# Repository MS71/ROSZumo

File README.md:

# ROSZumo
"second" Small robot based on ESP32 + ROS + ZUMO 32u4 base

Components:
* ZUMO32U4 Base (I2C Slave, Bat ADC, Motor Encoder, PWM for Lidar Stepper, l3gd20h, lsm303d, Line Sonsor, ...)
* ESP32CAM
* ESP32 WRoverwith CAM and SDCard
* driver and connector for rotating LIDAR
* 12x STM VL53L1X TOF sensor
* optional rotating Lidar with PCF8475+ULN2003 Stepper motor
* BNO055 Orientation Sensor
* STM32G081 uC
* connector for orange PI Zero H5
* connector for RPI SPI Display
* NIMH charger with front contacts
* SPI flash
* I2C level shifter
* I2C bus connector
* SPI bus connector
* low power design (shutdown and wakeup)
* optional Stereo/Quad SPI Camera

My Current Setup:
* Zumo AVR 32U4 
  * I2C slave
  * motor driver
  * bridge to all Zumo sensors (line sensor, beeper, IMU, ...)
  * battery pack 4xAA
  
* STM32G081
  * I2C slave
  * GPIO extender (e.g. for VL53L1X resets)
  * RPI LCD display driver
  * Battery changer
  * RTC
  * low power managment
  
* front VL53L1X as I2C slave

* ESP32Cam
  * I2C master
  * Camera
  * ROS2 Node
  * OTA firmware update
  
* external Linux PC or RPI3/4 as ROS2 master

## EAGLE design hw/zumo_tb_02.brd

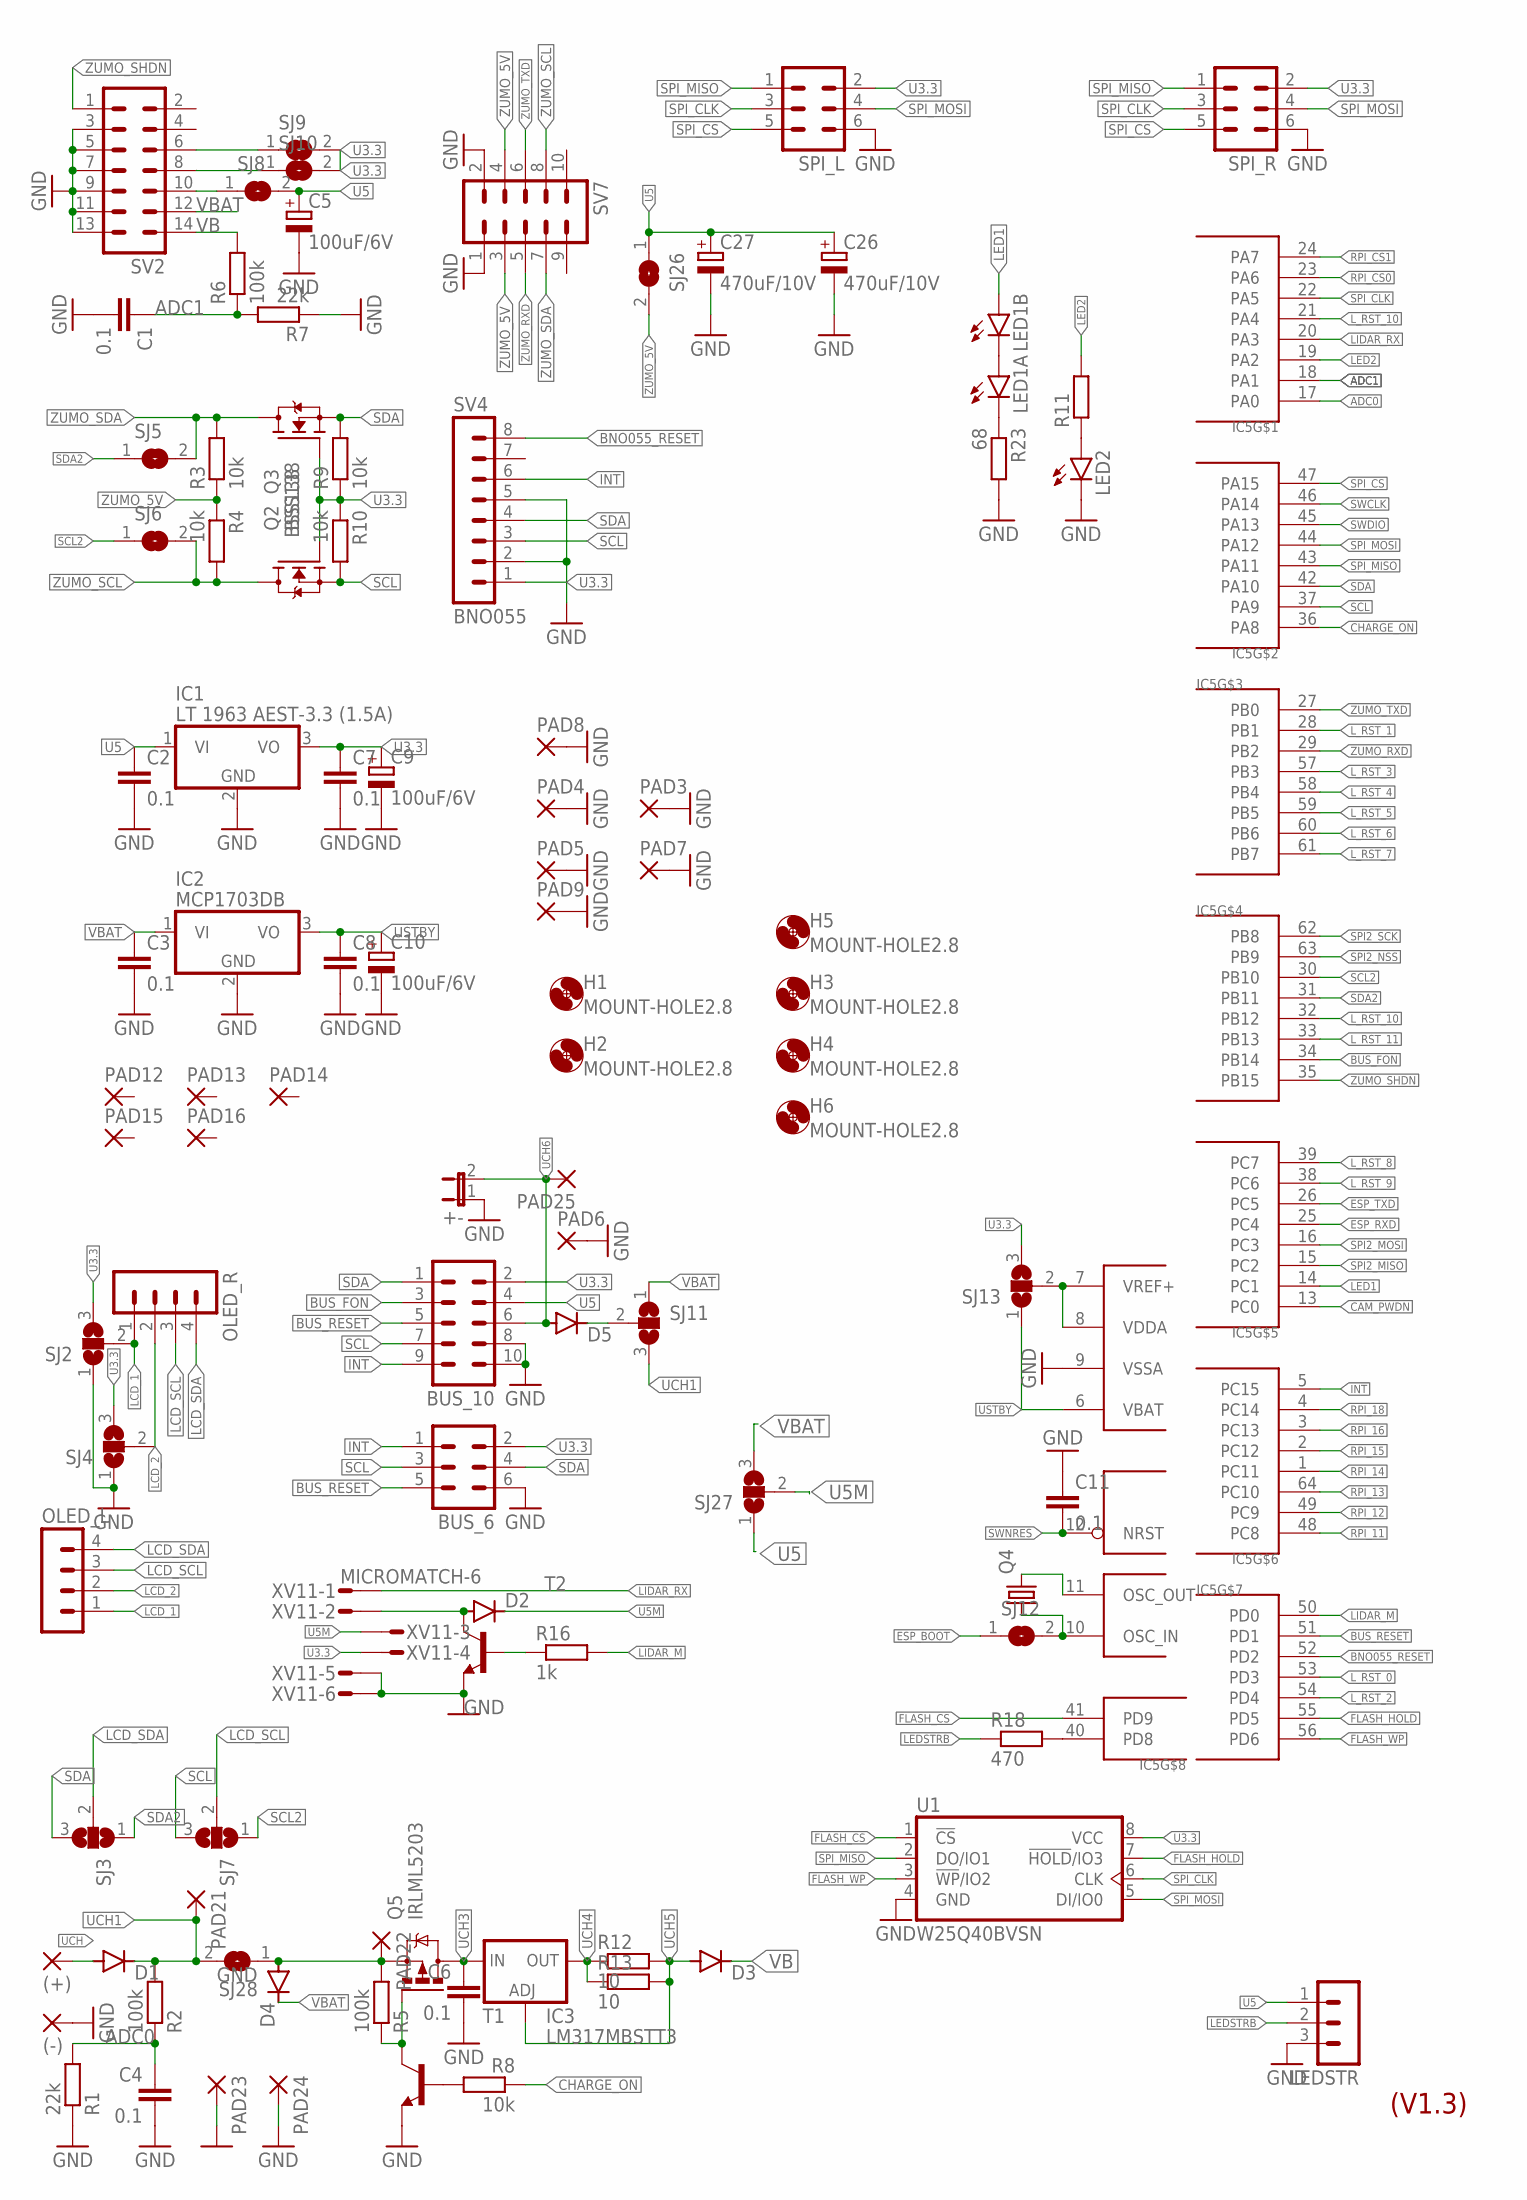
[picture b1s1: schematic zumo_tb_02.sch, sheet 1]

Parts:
(+): 3,81/1,4
(-): 3,81/1,4
+-: JP1E; JP1
BUS_6: ML6
BUS_10: ML10
C1, C2, C3, C4, C6, C7, C8, C11: 0.1; C0805
C5, C9, C10: 100uF/6V; B/3528-21R
C26, C27: 470uF/10V; SMC_D
D1, D3, D4, D5: DIODE-MELF-MLL41; MELF-MLL41
D2: DIODE-MINIMELF; MINIMELF
H1, H2, H3, H4, H5, H6: MOUNT-HOLE2.8; 2,8
IC1: LT 1963 AEST-3.3 (1.5A); SOT223
IC2: MCP1703DB; SOT223
IC3: LM317MBSTT3; SOT223
IC5: STM32G081RBT6; TQFP64
LED1A, LED1B: LED5MM
LED2: LEDCHIPLED_0805; CHIPLED_0805
LEDSTR: MA03-1
OLED_L: MA04-1
OLED_R: MA04-1
PAD3, PAD7, PAD9: 3,81/1,4
PAD4, PAD5, PAD6, PAD8: 2,15/1,0
PAD12, PAD13, PAD14, PAD15, PAD16, PAD25: 1,6/0,9
PAD21, PAD22, PAD23, PAD24: 1,6/0,8
Q2, Q3: BSS138; SOT23
Q4: CRYSTALTC26V; TC26V
Q5: IRLML5203; MICRO3
R1, R7: 22k; R0805
R2, R5, R6: 100k; R0805
R3, R4, R8, R9, R10: 10k; R0805
R11: R-EU_R0603; R0603
R12, R13: 10; R2010
R16: 1k; R0805
R18: 470; R0805
R23: 68; R0805
SJ2, SJ3, SJ4, SJ7, SJ11, SJ13, SJ27: SJ2W; SJ_2
SJ5, SJ6, SJ8, SJ9, SJ10, SJ12, SJ26, SJ28: SJ
SPI_L: ML6
SPI_R: ML6
SV2: MA07-2
SV4: BNO055; MA08-1
SV7: MA05-2
T1, T2: BC817-16-NPN-SOT23-BEC; SOT23-BEC
U1: W25Q40BVSN; SO08
XV11: MICROMATCH-6

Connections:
ADC0: C4.1, IC5.17 (PA0), R1.2, R2.1
ADC1: C1.1, IC5.18 (PA1), R6.1, R7.2
BNO055_RESET: IC5.52 (PD2), SV4.8
BUS_FON: BUS_10.3, IC5.34 (PB14)
BUS_RESET: BUS_6.5, BUS_10.5, IC5.51 (PD1)
CAM_PWDN: IC5.13 (PC0); also elsewhere on the board
CHARGE_ON: IC5.36 (PA8), R8.1
ESP_BOOT: SJ12.1; also elsewhere on the board
ESP_RXD: IC5.25 (PC4); also elsewhere on the board
ESP_TXD: IC5.26 (PC5); also elsewhere on the board
FLASH_CS: IC5.41 (PD9), U1.1 (!CS!)
FLASH_HOLD: IC5.55 (PD5), U1.7 (!HOLD!/IO3)
FLASH_WP: IC5.56 (PD6), U1.3 (!WP!/IO2)
GND: (-).1, +-.1, BUS_6.6, BUS_10.8, BUS_10.10, C1.2, C2.2, C3.2, C4.2, C5.-, C6.2, C7.2, C8.2, C9.-, C10.-, C11.1, C26.-, C27.-, IC1.2 (GND), IC2.2 (GND), IC5.9 (VSSA), LED2.C, LEDSTR.3, PAD3.1, PAD4.1, PAD5.1, PAD6.1, PAD7.1, PAD8.1, PAD9.1, PAD23.1, PAD24.1, R1.1, R7.1, R23.2, SJ2.1, SJ4.1, SPI_L.6, SPI_R.6, SV2.3, SV2.5, SV2.7, SV2.9, SV2.11, SV2.13, SV4.2, SV4.5, SV7.1, SV7.2, T1.E, T2.E, U1.4 (GND), XV11.5, XV11.6; also elsewhere on the board
INT: BUS_6.1, BUS_10.9, IC5.5 (PC15), SV4.6; also elsewhere on the board
LCD_1: OLED_L.1, OLED_R.1, SJ2.2
LCD_2: OLED_L.2, OLED_R.2, SJ4.2
LCD_SCL: OLED_L.3, OLED_R.3, SJ7.2
LCD_SDA: OLED_L.4, OLED_R.4, SJ3.2
LED1: IC5.14 (PC1), LED1B.A
LED2: IC5.19 (PA2), R11.2
LEDSTRB: LEDSTR.2, R18.1
LIDAR_M: IC5.50 (PD0), R16.2
LIDAR_RX: IC5.20 (PA3), XV11.1
L_RST_0: IC5.53 (PD3); also elsewhere on the board
L_RST_1: IC5.28 (PB1); also elsewhere on the board
L_RST_2: IC5.54 (PD4); also elsewhere on the board
L_RST_3: IC5.57 (PB3); also elsewhere on the board
L_RST_4: IC5.58 (PB4); also elsewhere on the board
L_RST_5: IC5.59 (PB5); also elsewhere on the board
L_RST_6: IC5.60 (PB6); also elsewhere on the board
L_RST_7: IC5.61 (PB7); also elsewhere on the board
L_RST_8: IC5.39 (PC7); also elsewhere on the board
L_RST_9: IC5.38 (PC6); also elsewhere on the board
L_RST_10: IC5.21 (PA4), IC5.32 (PB12); also elsewhere on the board
L_RST_11: IC5.33 (PB13); also elsewhere on the board
unnamed: IC5.11 (OSC_OUT), Q4.2
unnamed: IC5.10 (OSC_IN), Q4.1, SJ12.2
unnamed: IC5.40 (PD8), R18.2
unnamed: IC5.7 (VREF+), IC5.8 (VDDA), SJ13.2
unnamed: LED2.A, R11.1
unnamed: SJ10.1, SV2.8
unnamed: SJ9.1, SV2.6
unnamed: Q5.1 (G), R5.1, T1.C
unnamed: R8.2, T1.B
unnamed: R16.1, T2.B
unnamed: D5.C, SJ11.2
unnamed: LED1A.A, LED1B.K (C)
unnamed: LED1A.K (C), R23.1
unnamed: D2.A, T2.C, XV11.2
RPI_11: IC5.48 (PC8); also elsewhere on the board
RPI_12: IC5.49 (PC9); also elsewhere on the board
RPI_13: IC5.64 (PC10); also elsewhere on the board
RPI_14: IC5.1 (PC11); also elsewhere on the board
RPI_15: IC5.2 (PC12); also elsewhere on the board
RPI_16: IC5.3 (PC13); also elsewhere on the board
RPI_18: IC5.4 (PC14); also elsewhere on the board
RPI_CS0: IC5.23 (PA6); also elsewhere on the board
RPI_CS1: IC5.24 (PA7); also elsewhere on the board
SCL: BUS_6.3, BUS_10.7, IC5.37 (PA9), Q3.2 (S), R10.2, SJ7.3, SV4.3; also elsewhere on the board
SCL2: IC5.30 (PB10), SJ6.1, SJ7.1
SDA: BUS_6.4, BUS_10.1, IC5.42 (PA10), Q2.2 (S), R9.2, SJ3.3, SV4.4; also elsewhere on the board
SDA2: IC5.31 (PB11), SJ3.1, SJ5.1
SPI2_MISO: IC5.15 (PC2); also elsewhere on the board
SPI2_MOSI: IC5.16 (PC3); also elsewhere on the board
SPI2_NSS: IC5.63 (PB9); also elsewhere on the board
SPI2_SCK: IC5.62 (PB8); also elsewhere on the board
SPI_CLK: IC5.22 (PA5), SPI_L.3, SPI_R.3, U1.6 (CLK); also elsewhere on the board
SPI_CS: IC5.47 (PA15), SPI_L.5, SPI_R.5; also elsewhere on the board
SPI_MISO: IC5.43 (PA11), SPI_L.1, SPI_R.1, U1.2 (DO/IO1); also elsewhere on the board
SPI_MOSI: IC5.44 (PA12), SPI_L.4, SPI_R.4, U1.5 (DI/IO0); also elsewhere on the board
SWCLK: IC5.46 (PA14); also elsewhere on the board
SWDIO: IC5.45 (PA13); also elsewhere on the board
SWNRES: C11.2, IC5.12 (NRST); also elsewhere on the board
U3.3: BUS_6.2, BUS_10.2, C7.1, C9.+, IC1.3 (VO), Q2.1 (G), Q3.1 (G), R9.1, R10.1, SJ2.3, SJ4.3, SJ9.2, SJ10.2, SJ13.3, SPI_L.2, SPI_R.2, SV4.1, U1.8 (VCC), XV11.4; also elsewhere on the board
U5: BUS_10.4, C2.1, C5.+, C26.+, C27.+, IC1.1 (VI), LEDSTR.1, SJ8.2, SJ26.1, SJ27.1; also elsewhere on the board
U5M: D2.C, SJ27.2, XV11.3
UCH: (+).1, D1.A
UCH1: D1.C, PAD21.1, R2.2, SJ11.3, SJ28.2
UCH2: D4.A, PAD22.1, Q5.2 (S), R5.2, SJ28.1
UCH3: C6.1, IC3.3 (IN), Q5.3 (D)
UCH4: IC3.4 (OUT), R12.1, R13.1
UCH5: D3.A, IC3.1 (ADJ), R12.2, R13.2
UCH6: +-.2, BUS_10.6, D5.A, PAD25.1
USTBY: C8.1, C10.+, IC2.3 (VO), IC5.6 (VBAT), SJ13.1; also elsewhere on the board
VB: D3.C, R6.2, SV2.14
VBAT: C3.1, D4.C, IC2.1 (VI), SJ11.1, SJ27.3, SV2.12
VREG: SJ8.1, SV2.10
ZUMO_5V: R3.1, R4.1, SJ26.2, SV7.3, SV7.4
ZUMO_RXD: IC5.29 (PB2), SV7.5
ZUMO_SCL: Q3.3 (D), R4.2, SJ6.2, SV7.8
ZUMO_SDA: Q2.3 (D), R3.2, SJ5.2, SV7.7
ZUMO_SHDN: IC5.35 (PB15), SV2.1; also elsewhere on the board
ZUMO_TXD: IC5.27 (PB0), SV7.6

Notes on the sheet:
(V1.3)

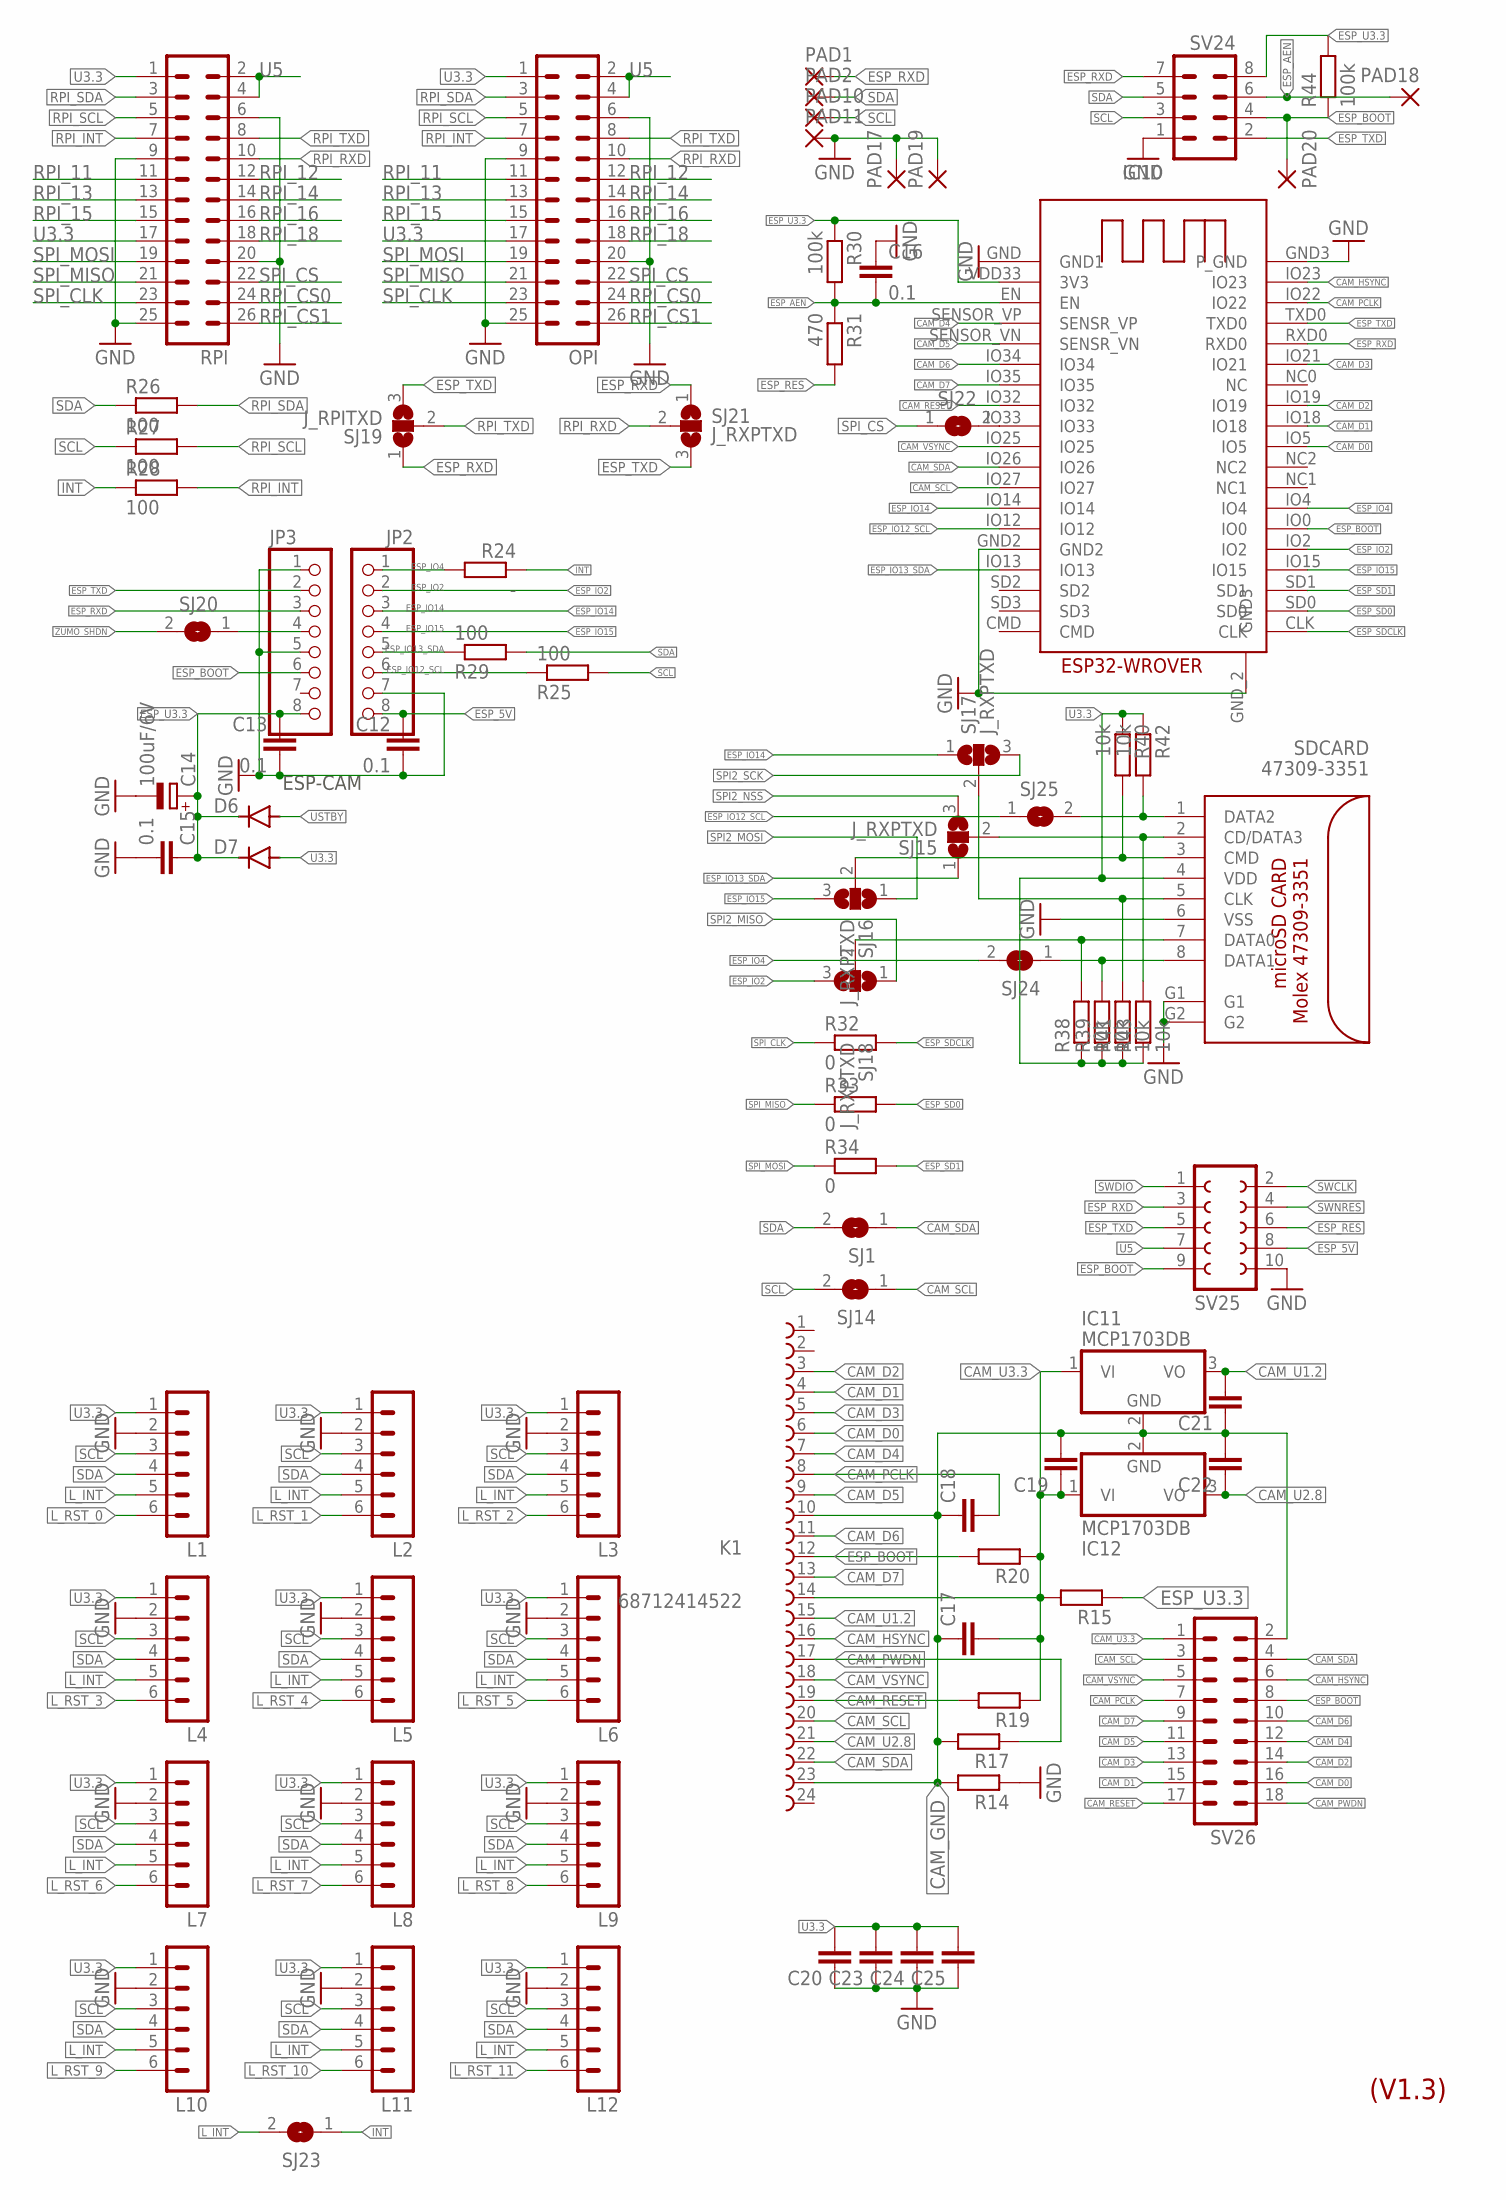
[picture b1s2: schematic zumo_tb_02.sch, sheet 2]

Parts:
C12, C13, C15, C16: 0.1; C0805
C14: 100uF/6V; B/3528-21R
C17, C18, C19, C20, C21, C22, C23, C24, C25: C-EUC0603; C0603
D6, D7: DIODE-MICROMELF-W; MICROMELF-W
IC10: ESP32-WROVER
IC11, IC12: MCP1703DB; SOT223
JP2, JP3: PINHD-1X8_2.54-SMD; 1X08SMD
K1: 68712414522
L1, L2, L3, L4, L5, L6, L7, L8, L9, L10, L11, L12: MA06-1
OPI: MA13-2
PAD1, PAD2, PAD10, PAD11, PAD17, PAD18, PAD19, PAD20: 1,6/0,9
R14, R15, R17, R19, R20: R-EU_R0603; R0603
R24: -; R0805
R25, R26, R27, R28, R29: 100; R0805
R30, R44: 100k; R0805
R31: 470; R0805
R32, R33, R34: 0; R0805
R38, R39, R40, R41, R42, R43: 10k; R0805
RPI: MA13-2
SDCARD: 47309-3351
SJ1, SJ14, SJ20, SJ22, SJ23, SJ24, SJ25: SJ
SJ15, SJ16, SJ17, SJ18, SJ21: J_RXPTXD; SJ_2
SJ19: J_RPITXD; SJ_2
SV24: MA04-2
SV25: FE05-2
SV26: MA09-2

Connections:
CAM_D0: IC10.IO5, K1.6, SV26.16
CAM_D1: IC10.IO18, K1.4, SV26.15
CAM_D2: IC10.IO19, K1.3, SV26.14
CAM_D3: IC10.IO21, K1.5, SV26.13
CAM_D4: IC10.SENSOR_VP (SENSR_VP), K1.7, SV26.12
CAM_D5: IC10.SENSOR_VN (SENSR_VN), K1.9, SV26.11
CAM_D6: IC10.IO34, K1.11, SV26.10
CAM_D7: IC10.IO35, K1.13, SV26.9
CAM_GND: C17.1, C18.1, C19.2, C21.1, C22.2, IC11.2 (GND), IC12.2 (GND), K1.10, K1.23, R14.2, R17.2, SV26.2
CAM_HSYNC: IC10.IO23, K1.16, SV26.6
CAM_PCLK: C18.2, IC10.IO22, K1.8, SV26.7
CAM_PWDN: K1.17, R17.1, SV26.18; also elsewhere on the board
CAM_RESET: IC10.IO32, K1.19, R19.2, SV26.17
CAM_SCL: IC10.IO27, K1.20, SJ14.1, SV26.3
CAM_SDA: IC10.IO26, K1.22, SJ1.1, SV26.4
CAM_U1.2: C21.2, IC11.3 (VO), K1.15
CAM_U2.8: C22.1, IC12.3 (VO), K1.21
CAM_U3.3: C17.2, C19.1, IC11.1 (VI), IC12.1 (VI), K1.14, R15.2, R19.1, R20.1, SV26.1
CAM_VSYNC: IC10.IO25, K1.18, SV26.5
ESPCAM_13: JP3.4, SJ20.1
ESP_5V: C12.1, JP2.8, SV25.8
ESP_AEN: C16.2, IC10.EN, PAD18.1, R30.2, R31.1, SV24.6
ESP_BOOT: IC10.IO0, JP3.6, K1.12, PAD20.1, R20.2, R44.1, SV24.4, SV25.9, SV26.8; also elsewhere on the board
ESP_IO2: IC10.IO2, JP2.2, SJ18.3
ESP_IO4: IC10.IO4, JP2.1, R24.2, SJ24.2
ESP_IO12_SCL: IC10.IO12, JP2.6, R25.1, SJ25.1
ESP_IO13_SDA: IC10.IO13, JP2.5, R29.1, SJ15.1
ESP_IO14: IC10.IO14, JP2.3, SJ17.1
ESP_IO15: IC10.IO15, JP2.4, SJ16.3
ESP_RES: R31.2, SV25.6
ESP_RXD: IC10.RXD0, JP3.3, PAD1.1, SJ19.1, SJ21.1, SV24.7, SV25.3; also elsewhere on the board
ESP_SD0: IC10.SD0, R33.2
ESP_SD1: IC10.SD1, R34.2
ESP_SDCLK: IC10.CLK, R32.2
ESP_TXD: IC10.TXD0, JP3.2, SJ19.3, SJ21.3, SV24.2, SV25.5; also elsewhere on the board
ESP_U3.3: C13.1, C14.+, C15.1, D6.C, D7.C, IC10.VDD33 (3V3), JP3.8, R15.1, R30.1, R44.2, SV24.8
GND: C12.2, C13.2, C14.-, C15.2, C16.1, C20.1, C23.1, C24.1, C25.1, IC10.GND (GND1), IC10.GND2, IC10.GND3 (P_GND), IC10.GND_2 (GND3), JP2.7, JP3.1, JP3.5, L1.2, L2.2, L3.2, L4.2, L5.2, L6.2, L7.2, L8.2, L9.2, L10.2, L11.2, L12.2, OPI.6, OPI.9, OPI.20, OPI.25, PAD11.1, PAD17.1, PAD19.1, R14.1, RPI.6, RPI.9, RPI.20, RPI.25, SDCARD.6 (VSS), SDCARD.G1, SDCARD.G2, SV24.1, SV25.10; also elsewhere on the board
INT: R24.1, R28.1, SJ23.1; also elsewhere on the board
L_INT: L1.5, L2.5, L3.5, L4.5, L5.5, L6.5, L7.5, L8.5, L9.5, L10.5, L11.5, L12.5, SJ23.2
L_RST_0: L1.6; also elsewhere on the board
L_RST_1: L2.6; also elsewhere on the board
L_RST_2: L3.6; also elsewhere on the board
L_RST_3: L4.6; also elsewhere on the board
L_RST_4: L5.6; also elsewhere on the board
L_RST_5: L6.6; also elsewhere on the board
L_RST_6: L7.6; also elsewhere on the board
L_RST_7: L8.6; also elsewhere on the board
L_RST_8: L9.6; also elsewhere on the board
L_RST_9: L10.6; also elsewhere on the board
L_RST_10: L11.6; also elsewhere on the board
L_RST_11: L12.6; also elsewhere on the board
unnamed: IC10.IO33, SJ22.2
RPI_11: OPI.11, RPI.11; also elsewhere on the board
RPI_12: OPI.12, RPI.12; also elsewhere on the board
RPI_13: OPI.13, RPI.13; also elsewhere on the board
RPI_14: OPI.14, RPI.14; also elsewhere on the board
RPI_15: OPI.15, RPI.15; also elsewhere on the board
RPI_16: OPI.16, RPI.16; also elsewhere on the board
RPI_18: OPI.18, RPI.18; also elsewhere on the board
RPI_CS0: OPI.24, RPI.24; also elsewhere on the board
RPI_CS1: OPI.26, RPI.26; also elsewhere on the board
RPI_INT: OPI.7, R28.2, RPI.7
RPI_RXD: OPI.10, RPI.10, SJ21.2
RPI_SCL: OPI.5, R27.2, RPI.5
RPI_SDA: OPI.3, R26.2, RPI.3
RPI_TXD: OPI.8, RPI.8, SJ19.2
SCL: L1.3, L2.3, L3.3, L4.3, L5.3, L6.3, L7.3, L8.3, L9.3, L10.3, L11.3, L12.3, PAD10.1, R25.2, R27.1, SJ14.2, SV24.3; also elsewhere on the board
SDA: L1.4, L2.4, L3.4, L4.4, L5.4, L6.4, L7.4, L8.4, L9.4, L10.4, L11.4, L12.4, PAD2.1, R26.1, R29.2, SJ1.2, SV24.5; also elsewhere on the board
SD_CLK: R41.2, SDCARD.5 (CLK), SJ17.2
SD_CMD: R40.2, SDCARD.3 (CMD), SJ16.2
SD_DAT0: R38.2, SDCARD.7 (DATA0), SJ18.2
SD_DAT1: R39.2, SDCARD.8 (DATA1), SJ24.1
SD_DAT2: R42.2, SDCARD.1 (DATA2), SJ25.2
SD_DAT3: R43.2, SDCARD.2 (CD/DATA3), SJ15.2
SPI2_MISO: SJ18.1; also elsewhere on the board
SPI2_MOSI: SJ16.1; also elsewhere on the board
SPI2_NSS: SJ15.3; also elsewhere on the board
SPI2_SCK: SJ17.3; also elsewhere on the board
SPI_CLK: OPI.23, R32.1, RPI.23; also elsewhere on the board
SPI_CS: OPI.22, RPI.22, SJ22.1; also elsewhere on the board
SPI_MISO: OPI.21, R33.1, RPI.21; also elsewhere on the board
SPI_MOSI: OPI.19, R34.1, RPI.19; also elsewhere on the board
SWCLK: SV25.2; also elsewhere on the board
SWDIO: SV25.1; also elsewhere on the board
SWNRES: SV25.4; also elsewhere on the board
U3.3: C20.2, C23.2, C24.2, C25.2, D7.A, L1.1, L2.1, L3.1, L4.1, L5.1, L6.1, L7.1, L8.1, L9.1, L10.1, L11.1, L12.1, OPI.1, OPI.17, R38.1, R39.1, R40.1, R41.1, R42.1, R43.1, RPI.1, RPI.17, SDCARD.4 (VDD); also elsewhere on the board
U5: OPI.2, OPI.4, RPI.2, RPI.4, SV25.7; also elsewhere on the board
USTBY: D6.A; also elsewhere on the board
ZUMO_SHDN: SJ20.2; also elsewhere on the board

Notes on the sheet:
ESP-CAM
(V1.3)

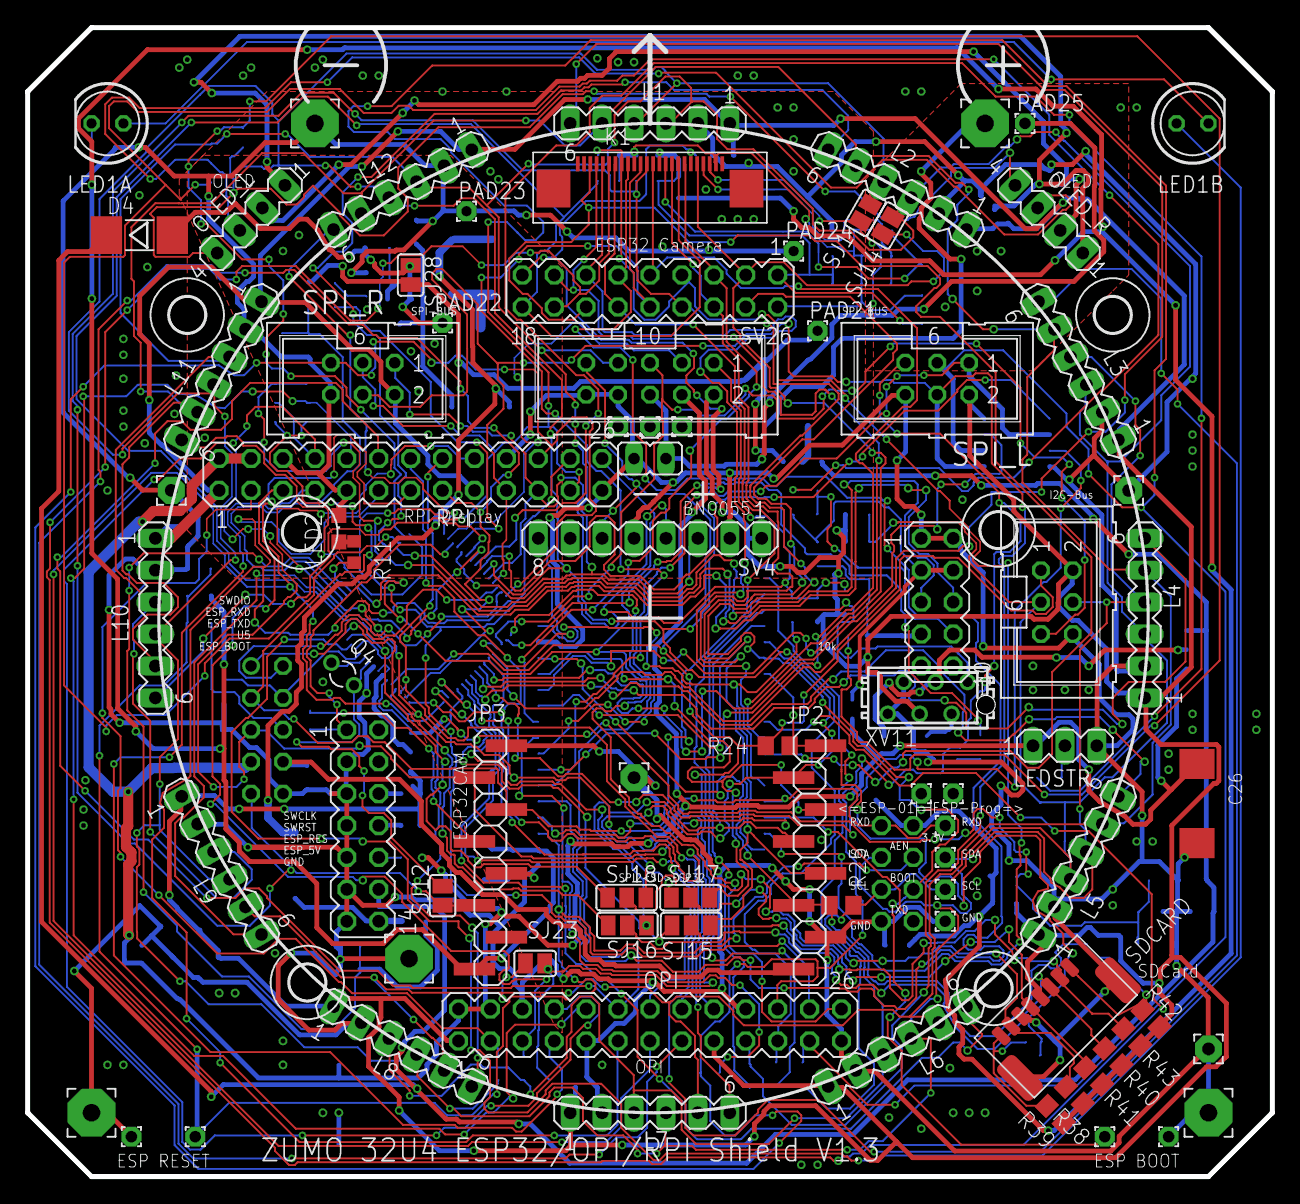
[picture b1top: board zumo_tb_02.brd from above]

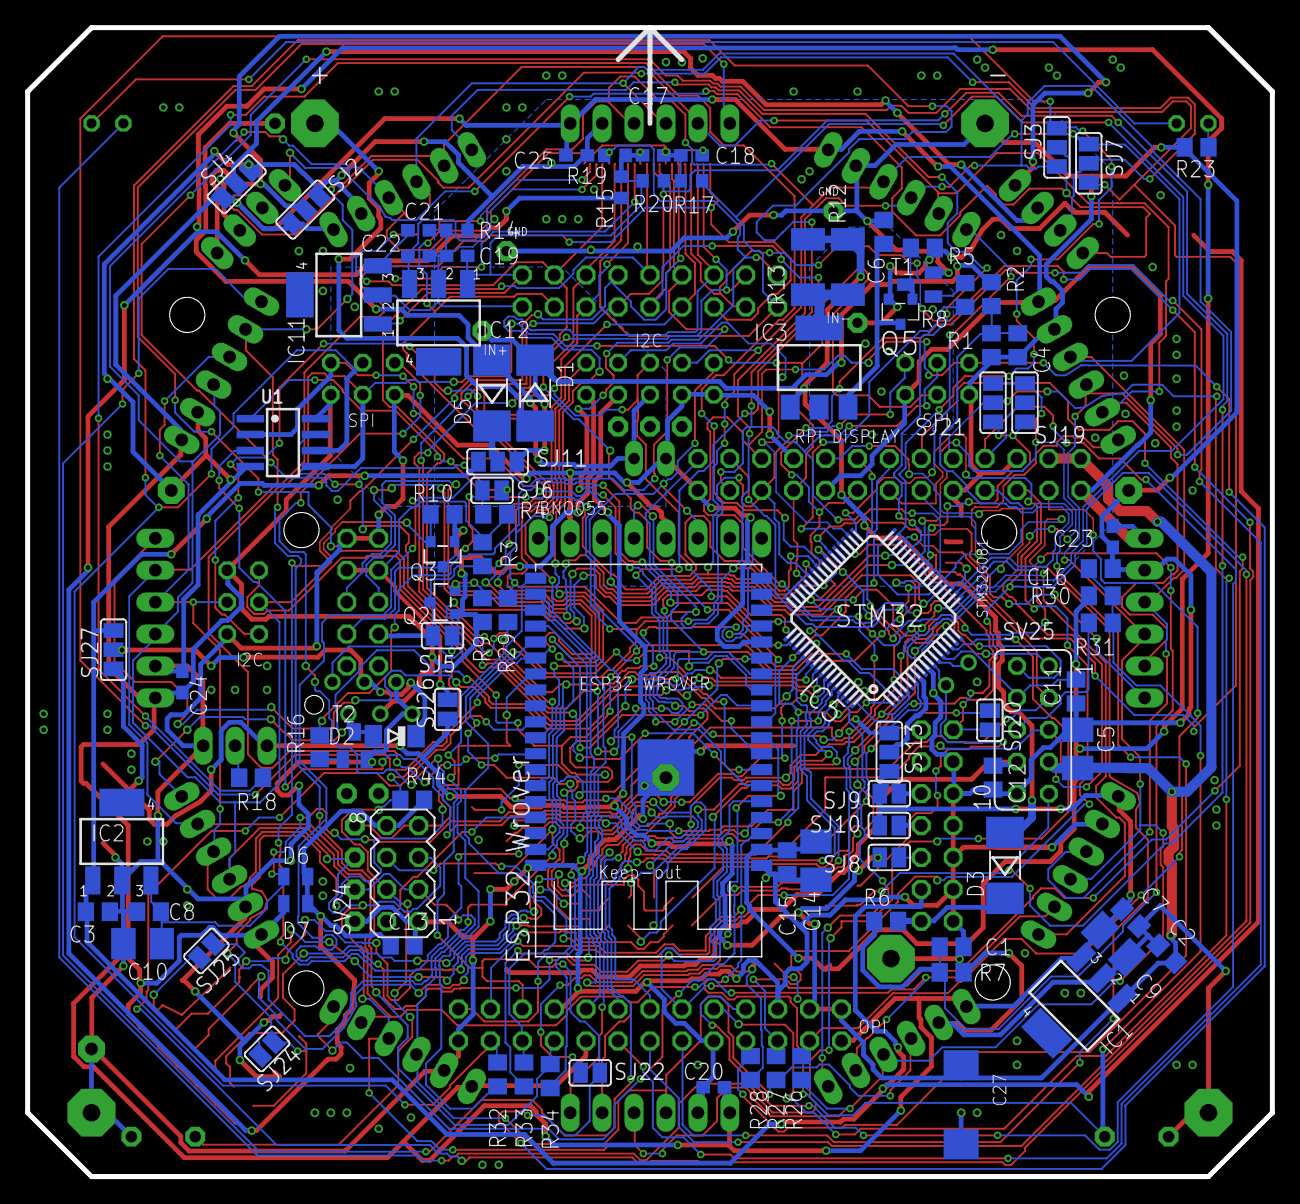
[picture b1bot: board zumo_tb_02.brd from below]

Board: 2 copper layers, 99.1 x 91.4 mm, 184 parts (96 on the bottom side), 139 nets.

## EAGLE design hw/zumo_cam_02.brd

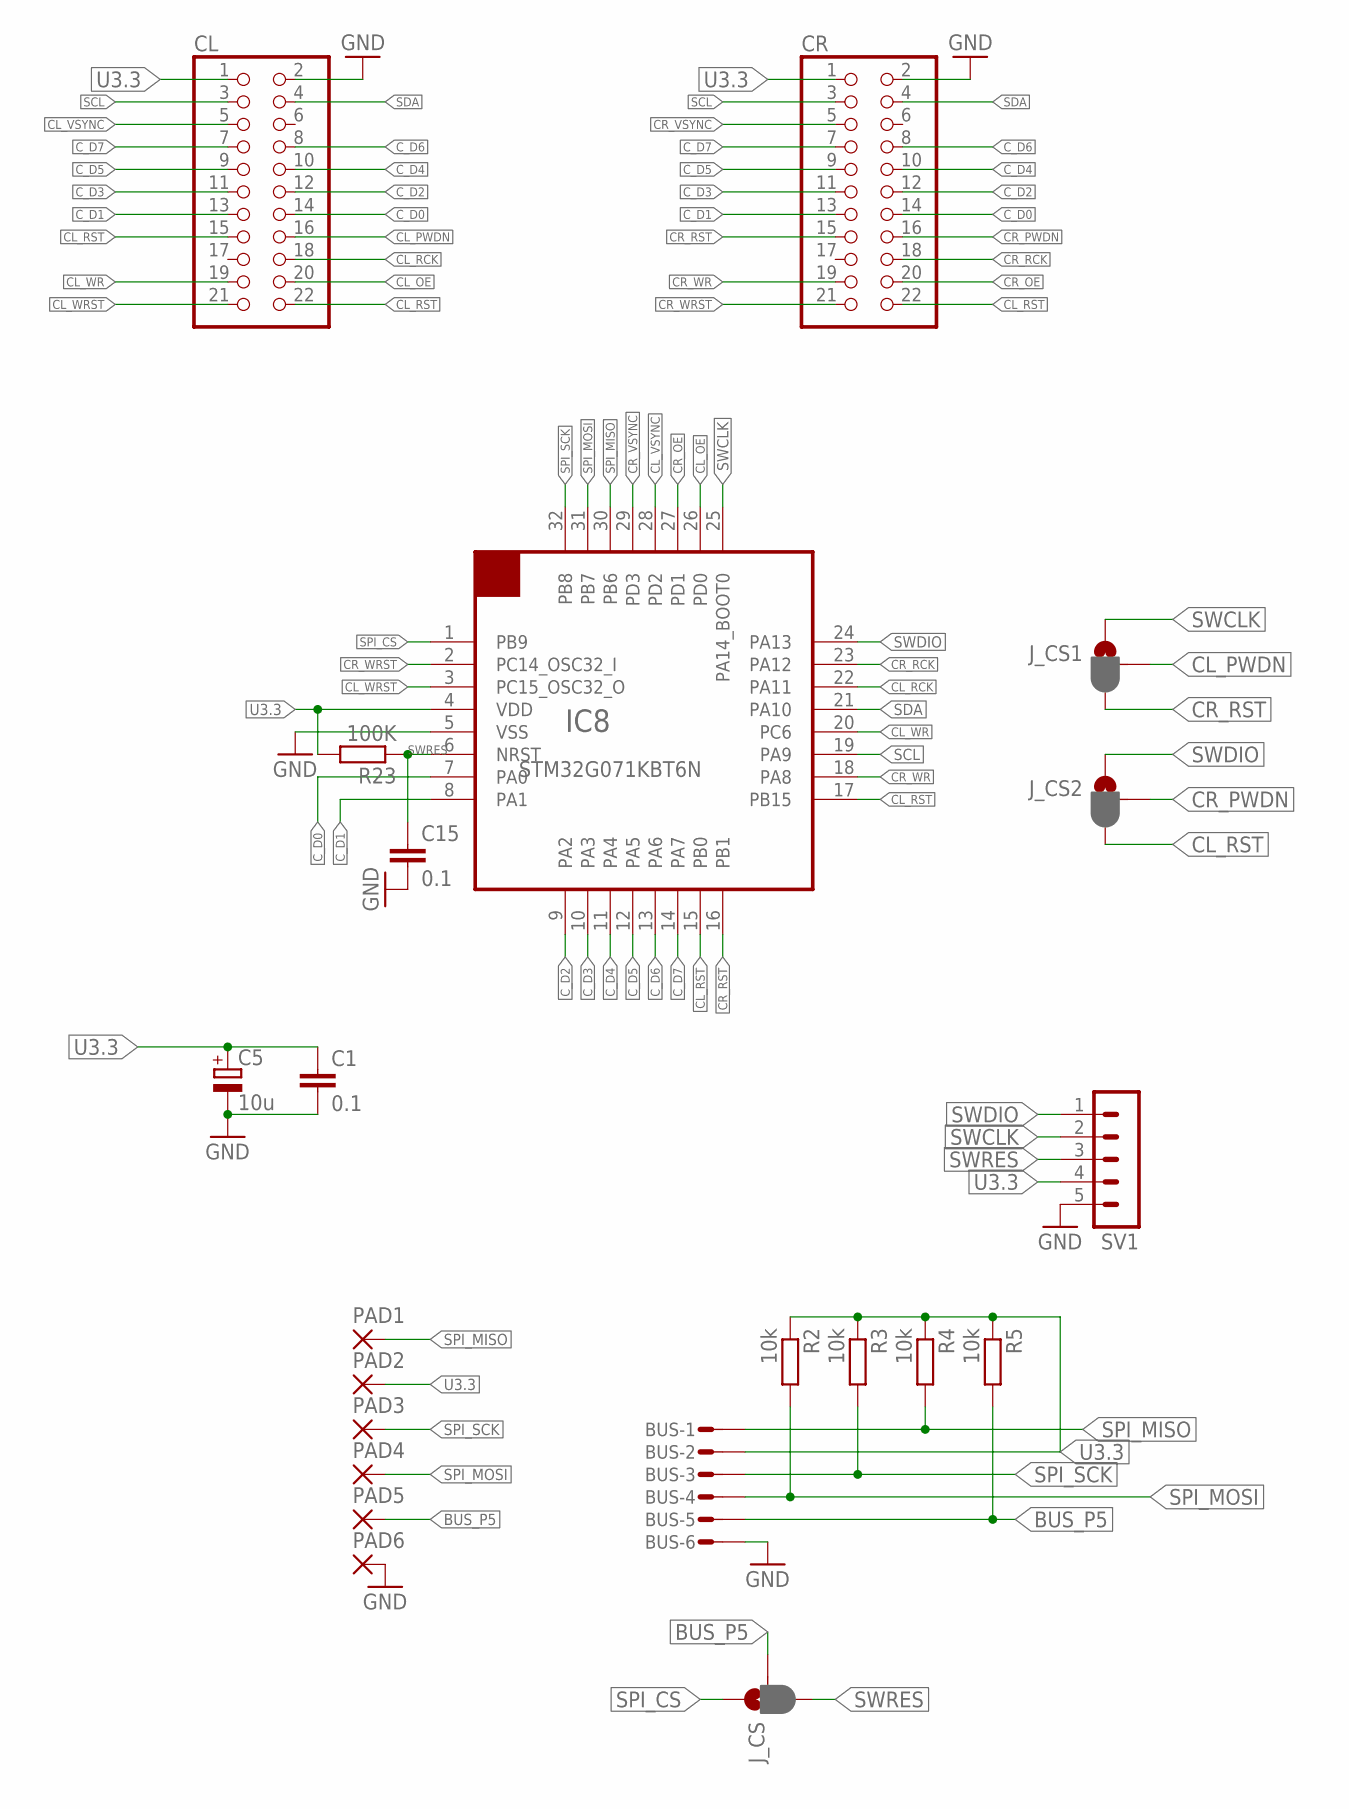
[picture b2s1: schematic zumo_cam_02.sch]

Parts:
BUS: MICROMATCH-6SMD
C1, C15: 0.1; C0805
C5: 10u; B/3528-21W
CL: PINHD-2X11_2.54-SMD; 2X11SMD
CR: PINHD-2X11_2.54-SMD; 2X11SMD
IC8: STM32G071KBT6N; LQFP-32
J_CS, J_CS1, J_CS2: JUMPER-SMT_3_1-NC_PASTE_NO-SILK; SMT-JUMPER_3_1-NC_PASTE_NO-SILK
PAD1, PAD2, PAD3, PAD4, PAD5, PAD6: SMD2; SMD1,27-2,54
R2, R3, R4, R5: 10k; M0805
R23: 100K; R0805
SV1: MA05-1

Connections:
BUS_P5: BUS.5, J_CS.2, PAD5.1, R5.2
CL_OE: CL.20, IC8.26 (PD0)
CL_PWDN: CL.16, J_CS1.2
CL_RCK: CL.18, IC8.22 (PA11)
CL_RST: CL.15, CL.22, CR.22, IC8.15 (PB0), IC8.17 (PB15), J_CS2.3
CL_VSYNC: CL.5, IC8.28 (PD2)
CL_WR: CL.19, IC8.20 (PC6)
CL_WRST: CL.21, IC8.3 (PC15_OSC32_O)
CR_OE: CR.20, IC8.27 (PD1)
CR_PWDN: CR.16, J_CS2.2
CR_RCK: CR.18, IC8.23 (PA12)
CR_RST: CR.15, IC8.16 (PB1), J_CS1.3
CR_VSYNC: CR.5, IC8.29 (PD3)
CR_WR: CR.19, IC8.18 (PA8)
CR_WRST: CR.21, IC8.2 (PC14_OSC32_I)
C_D0: CL.14, CR.14, IC8.7 (PA0)
C_D1: CL.13, CR.13, IC8.8 (PA1)
C_D2: CL.12, CR.12, IC8.9 (PA2)
C_D3: CL.11, CR.11, IC8.10 (PA3)
C_D4: CL.10, CR.10, IC8.11 (PA4)
C_D5: CL.9, CR.9, IC8.12 (PA5)
C_D6: CL.8, CR.8, IC8.13 (PA6)
C_D7: CL.7, CR.7, IC8.14 (PA7)
GND: BUS.6, C1.2, C5.-, C15.2, CL.2, CR.2, IC8.5 (VSS), PAD6.1, SV1.5
SCL: CL.3, CR.3, IC8.19 (PA9)
SDA: CL.4, CR.4, IC8.21 (PA10)
SPI_CS: IC8.1 (PB9), J_CS.1
SPI_MISO: BUS.1, IC8.30 (PB6), PAD1.1, R4.2
SPI_MOSI: BUS.4, IC8.31 (PB7), PAD4.1, R2.2
SPI_SCK: BUS.3, IC8.32 (PB8), PAD3.1, R3.2
SWCLK: IC8.25 (PA14_BOOT0), J_CS1.1, SV1.2
SWDIO: IC8.24 (PA13), J_CS2.1, SV1.1
SWRES: C15.1, IC8.6 (NRST), J_CS.3, R23.1, SV1.3
U3.3: BUS.2, C1.1, C5.+, CL.1, CR.1, IC8.4 (VDD), PAD2.1, R2.1, R3.1, R4.1, R5.1, R23.2, SV1.4

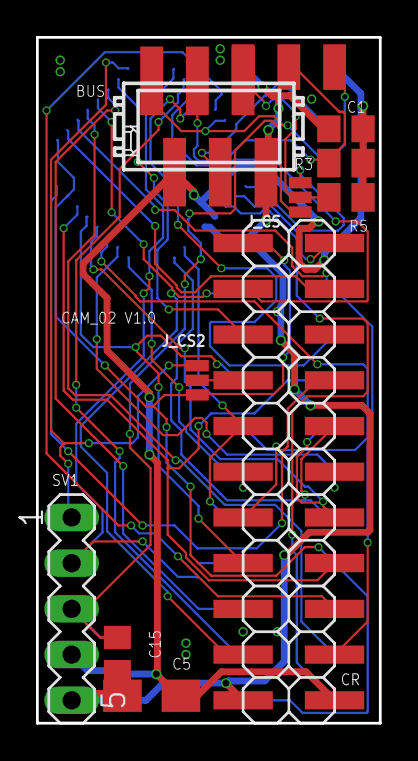
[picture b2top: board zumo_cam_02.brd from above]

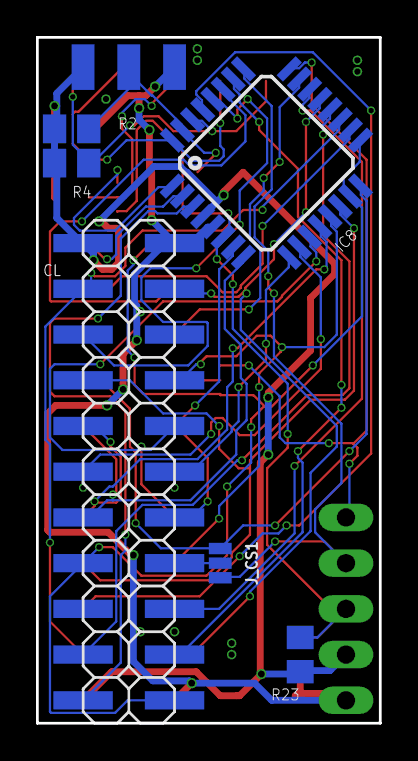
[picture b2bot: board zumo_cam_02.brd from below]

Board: 2 copper layers, 19.1 x 38.1 mm, 22 parts (9 on the bottom side), 34 nets.

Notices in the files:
parts and their libraries:
diy-modules: Released under the Creative Commons Attribution 4.0 International License: http://creativecommons.org/licenses/by/4.0
SparkFun-Jumpers: Licensing: Creative Commons ShareAlike 4.0 International - https://creativecommons.org/licenses/by-sa/4.0
